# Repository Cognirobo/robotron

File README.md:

# robotron
our first own robot

Welcome to our robotron!!
Here we can handle all documents, scripts and code for our robot
Here is a basic stucture, please feel free to add, edit and extend if it is needed.

**Vision statement:**
We will build a powerful and adaptable Robotplatform 

* Projcect Plan
  * Who is Who and what to do
  * Ideas for the robot and the future
* Mechanical design
  * Calculations and requirements
  * Blueprints for the robot
  * Pictures
* Electrical design
  * Wireing
  * Blueprints of the electrical circuts
  * Pictures
* Code
  * :-) a hell lot of code in c, c++, phyton etc.
* Frond design 
  * drawings how the robot will look
  * Pictures 

**Price**
For all of you who not studied buissnes stuff. The price is important. Make a good robot with cheap stuff then it will be fantastic with expensive components.

**RoboLution:** Here everyone can see what we have after each Hackday, this we call the RoboLution.

* fist Hackday
https://github.com/Cognirobo/robotron/blob/master/projectplan/2016_04_23_Hackday/images/RoboLution_1.avi

* second Hackday
https://github.com/Cognirobo/robotron/blob/master/projectplan/2016_05_16_Hackday/images/RoboLution_2.avi

* third Hackday
https://github.com/Cognirobo/robotron/blob/master/projectplan/2016_05_26_Hackday/images/RoboLution_3.avi

* fourth Hackday
https://github.com/Cognirobo/robotron/blob/master/projectplan/2016_06_19_Hackday/images/RoboLution_4.avi

**Have fun with Markdown to make it look really cool**
  
https://guides.github.com/features/mastering-markdown/

**Nice tool for windows to see the branches and commits**

https://desktop.github.com/

**Nice tool to make UML and other charts**

http://de.plantuml.com/
and the online version:
http://www.planttext.com/planttext

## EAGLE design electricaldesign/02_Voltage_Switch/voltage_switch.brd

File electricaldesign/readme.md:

#Proposal for the Powersupply

In order to work good with the robot,
As a developer I need to connect the robot to a 230V energy supply or a battery.

Side conditions:
* switch from battery to main voltage when the 230V supply is connected
* has until now two different current levels: 
  * approximal 15 V for Arduino and elecrtical drive
  * approximal 5 V for everything with USB PI
* overall energy consumption is not clear and has to be investigated

Plaesa note: The files with the ending .sch can be opend via eagle

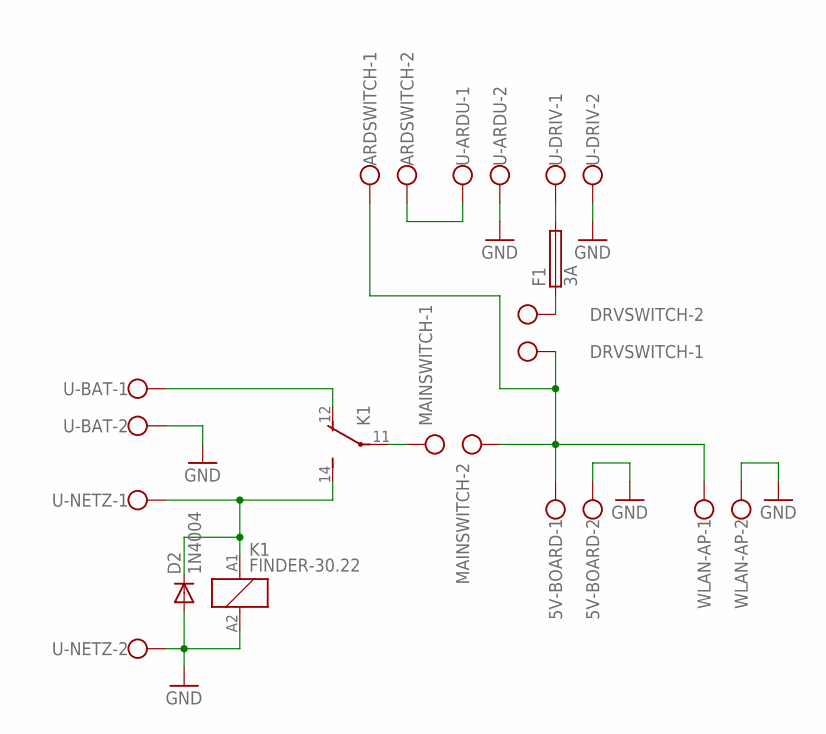
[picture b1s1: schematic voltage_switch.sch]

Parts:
5V-BOARD: W237-102
ARDSWITCH: W237-102
D2: 1N4004; DO41-10
DRVSWITCH: W237-102
F1: 3A; GSH15
K1: FINDER-30.22
MAINSWITCH: W237-102
U-ARDU: W237-102
U-BAT: W237-102
U-DRIV: W237-102
U-NETZ: W237-102
WLAN-AP: W237-102

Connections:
GND: 5V-BOARD.2, D2.A, K1.A2 (2), U-ARDU.2, U-BAT.2, U-DRIV.2, U-NETZ.2, WLAN-AP.2
unnamed: D2.C, K1.14 (S), K1.A1 (1), U-NETZ.1
unnamed: K1.11, MAINSWITCH.1
unnamed: K1.12 (O), U-BAT.1
unnamed: DRVSWITCH.2, F1.1
unnamed: 5V-BOARD.1, ARDSWITCH.1, DRVSWITCH.1, MAINSWITCH.2, WLAN-AP.1
unnamed: F1.2, U-DRIV.1
unnamed: ARDSWITCH.2, U-ARDU.1

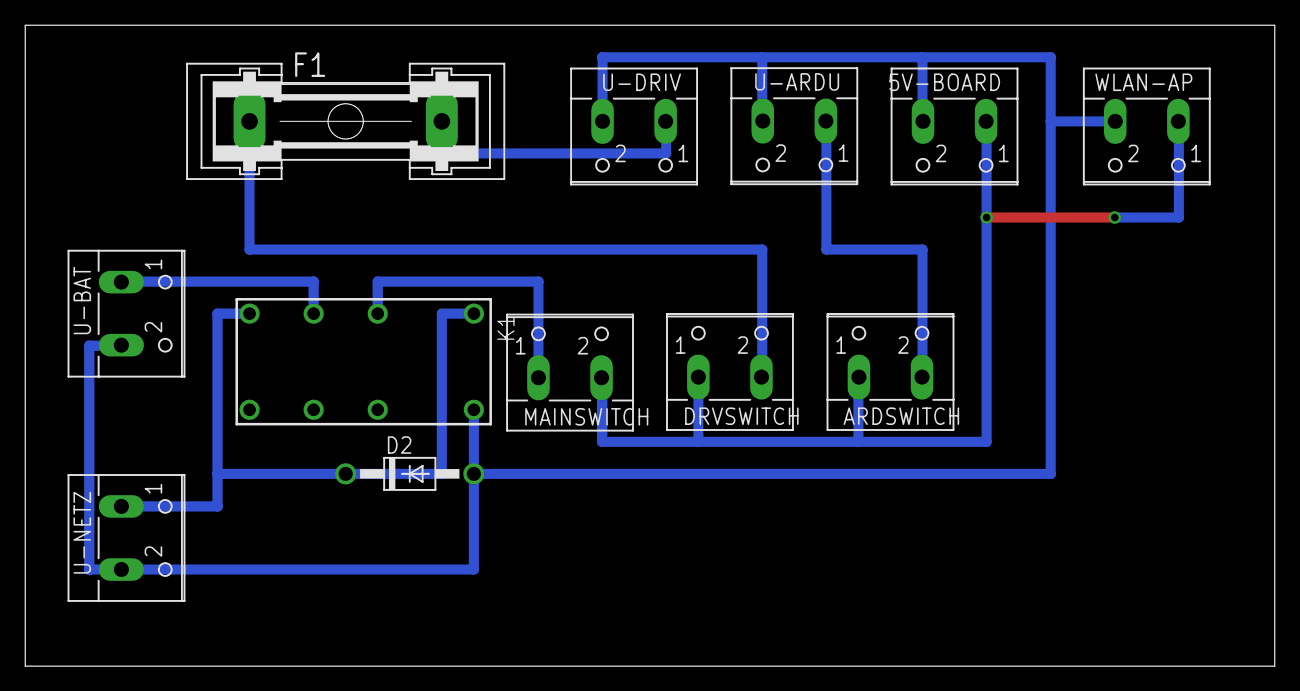
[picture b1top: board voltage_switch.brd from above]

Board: 2 copper layers, 99.0 x 50.8 mm, 12 parts (0 on the bottom side), 8 nets.

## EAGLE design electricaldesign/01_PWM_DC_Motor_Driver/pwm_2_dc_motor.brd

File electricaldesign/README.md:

#Electrical Hardware
There are several boards we need to use our robotron. They are so far:

###PWM DC Motor driver
Uses a PWM signal to drive the two DC motors. Can handle up to 50A and 20V, but needs a cooling device on top.

###Voltage distribution
Gets the voltage to every part of our robotron and is the central board to plugin the batteries or the main supply.

###5V DC
Step-down-regulator to get 5V for the Raspberry Pi.

###Encoder of wheel rpm
Produces a signal with a infrared diode and a infrared transistor so the rpm of ever wheel can be read by the arduino and our robot will drive the way we want it. One board per wheel, but the schematics are the same.

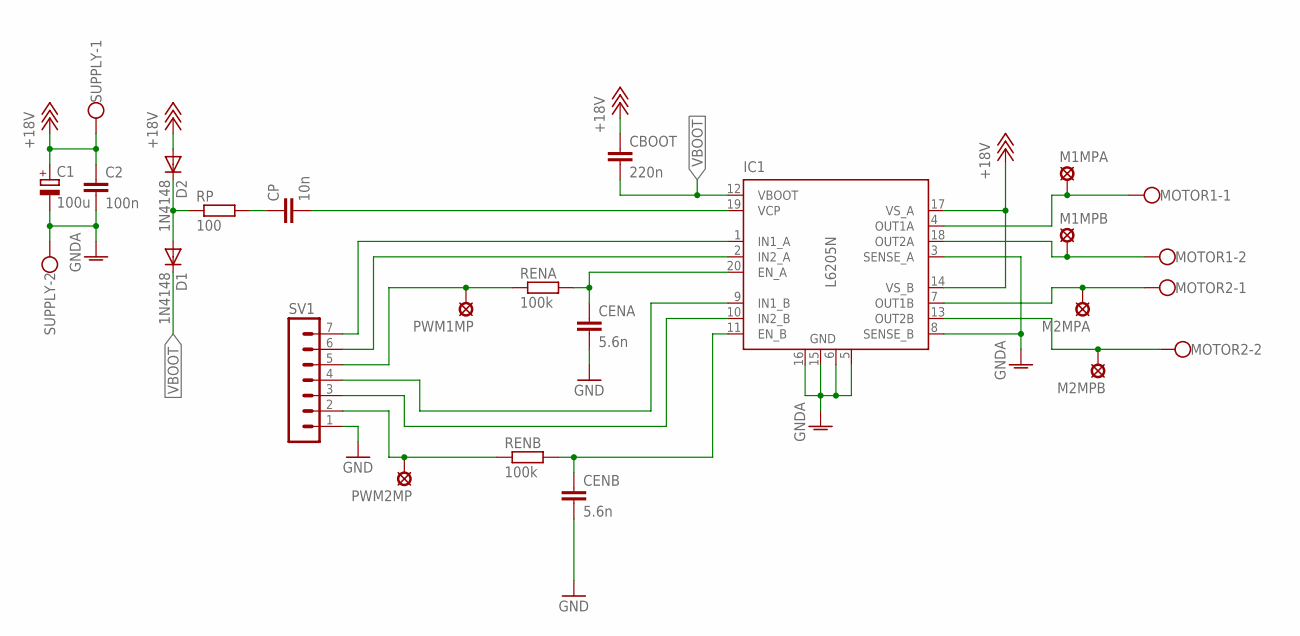
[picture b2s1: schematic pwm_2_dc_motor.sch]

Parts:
C1: 100u; E2,5-6E
C2: 100n; C025-025X050
CBOOT: 220n; C025-025X050
CENA: 5.6n; C025-025X050
CENB: 5.6n; C025-025X050
CP: 10n; C025-025X050
D1, D2: 1N4148; DO35-10
IC1: L6205N; DIL20
M1MPA, M1MPB, M2MPA, M2MPB: LSP10
MOTOR1, MOTOR2: W237-102
PWM1MP, PWM2MP: LSP10
RENA: 100k; 0207/10
RENB: 100k; 0207/10
RP: 100; 0207/12
SUPPLY: W237-102
SV1: MA07-1

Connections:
+18V: C1.+, C2.1, CBOOT.1, D2.A, IC1.14 (VS_B), IC1.17 (VS_A), SUPPLY.1
GND: CENA.2, CENB.2, SV1.1
GNDA: C1.-, C2.2, IC1.3 (SENSE_A), IC1.5 (GND), IC1.6 (GND), IC1.8 (SENSE_B), IC1.15 (GND), IC1.16 (GND), SUPPLY.2
unnamed: IC1.4 (OUT1A), M1MPA.MP, MOTOR1.1
unnamed: IC1.1 (IN1_A), SV1.7
unnamed: IC1.2 (IN2_A), SV1.6
unnamed: PWM1MP.MP, RENA.1, SV1.5
unnamed: IC1.9 (IN1_B), SV1.4
unnamed: IC1.10 (IN2_B), SV1.3
unnamed: CENA.1, IC1.20 (EN_A), RENA.2
unnamed: D1.A, D2.C, RP.1
unnamed: CP.1, RP.2
unnamed: CP.2, IC1.19 (VCP)
unnamed: IC1.18 (OUT2A), M1MPB.MP, MOTOR1.2
unnamed: IC1.7 (OUT1B), M2MPA.MP, MOTOR2.1
unnamed: IC1.13 (OUT2B), M2MPB.MP, MOTOR2.2
unnamed: CENB.1, IC1.11 (EN_B), RENB.2
unnamed: PWM2MP.MP, RENB.1, SV1.2
VBOOT: CBOOT.2, D1.C, IC1.12 (VBOOT)

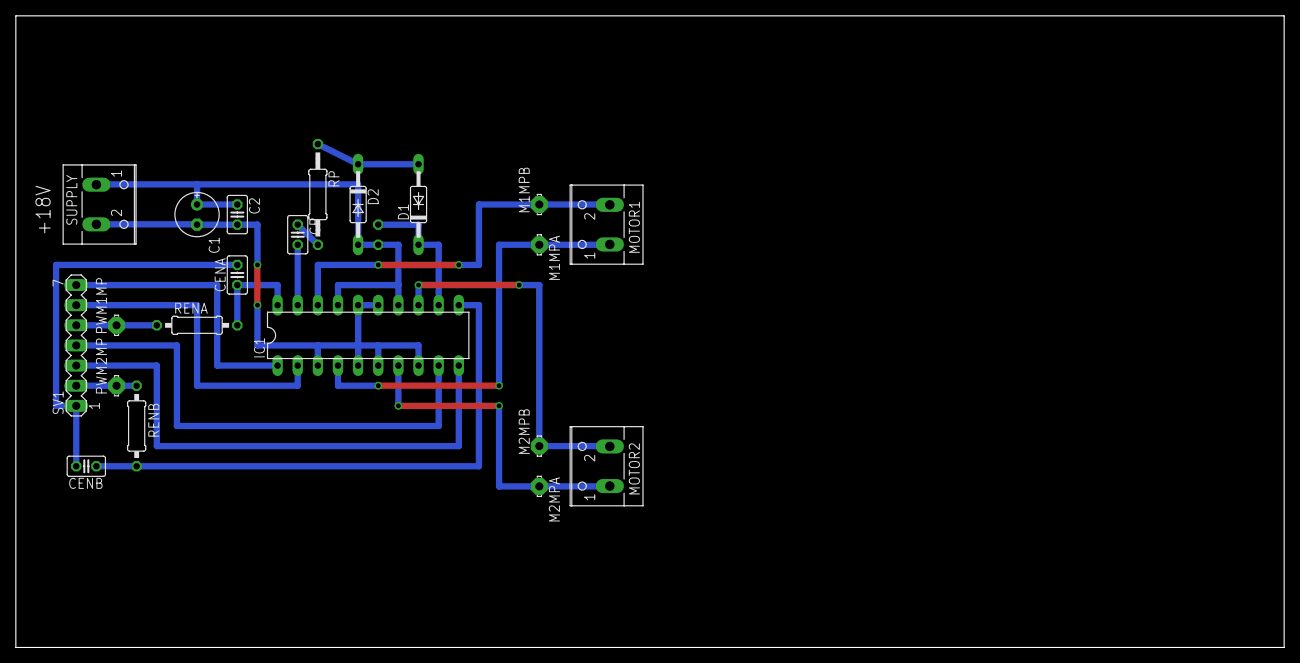
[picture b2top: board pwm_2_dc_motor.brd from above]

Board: 2 copper layers, 160.0 x 79.7 mm, 22 parts (1 on the bottom side), 19 nets.

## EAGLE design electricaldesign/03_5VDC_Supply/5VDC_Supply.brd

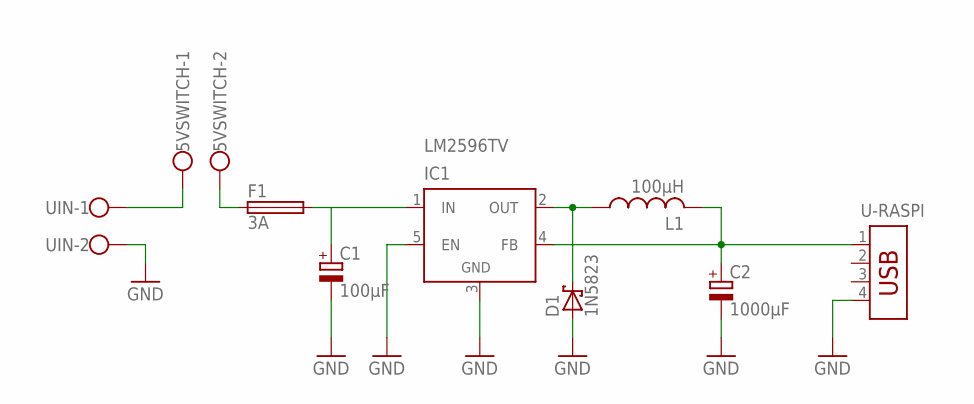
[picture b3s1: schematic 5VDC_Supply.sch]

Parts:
5VSWITCH: W237-102
C1: 100µF; E5-6
C2: 1000µF; E5-10,5
D1: 1N5823; C4111-15
F1: 3A; GSH15
IC1: LM2596TV; TO220-51
L1: 100µH; IRF-3
U-RASPI: USB-787616; USB
UIN: W237-102

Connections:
GND: C1.-, C2.-, D1.A, IC1.3 (GND), IC1.5 (EN), U-RASPI.4, UIN.2
unnamed: 5VSWITCH.1, UIN.1
unnamed: 5VSWITCH.2, F1.1
unnamed: C1.+, F1.2, IC1.1 (IN)
unnamed: D1.C, IC1.2 (OUT), L1.1
unnamed: C2.+, IC1.4 (FB), L1.2, U-RASPI.1

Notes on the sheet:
LM2596TV

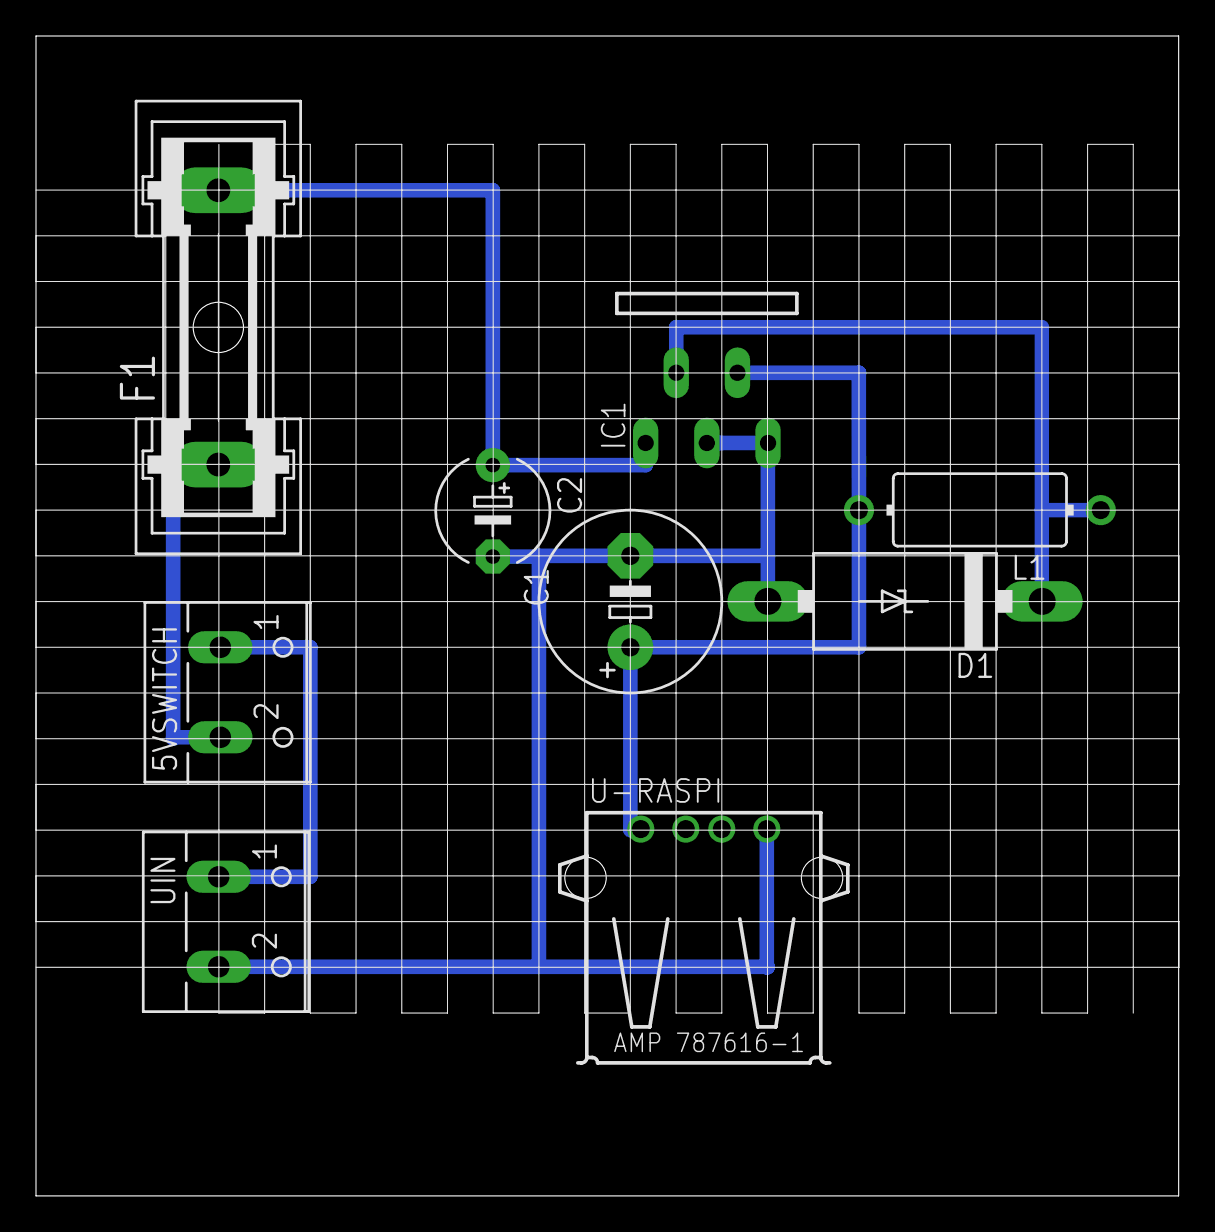
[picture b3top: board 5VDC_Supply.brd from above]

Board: 2 copper layers, 63.5 x 64.4 mm, 9 parts (0 on the bottom side), 6 nets.

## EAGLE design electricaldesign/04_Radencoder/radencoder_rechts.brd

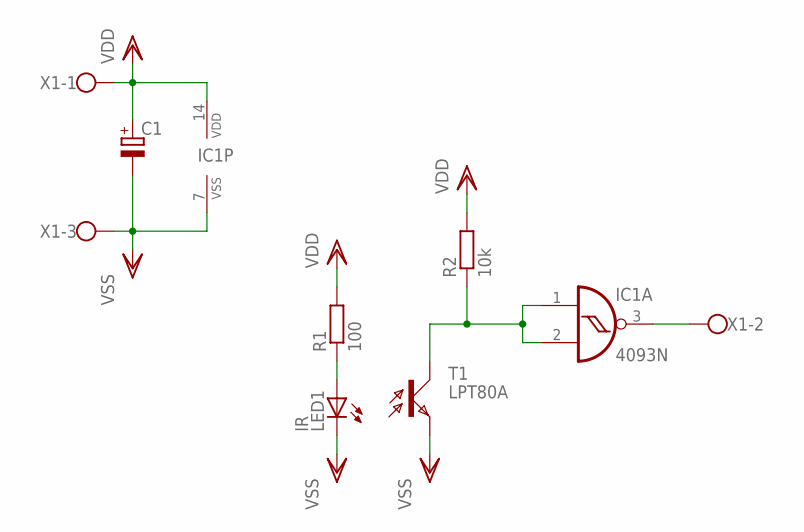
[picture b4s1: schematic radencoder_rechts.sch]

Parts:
C1: CPOL-EUE5-10.5; E5-10,5
IC1: 4093N; DIL14
LED1: IR; LED5MM
R1: 100; 0207/10
R2: 10k; 0207/10
T1: LPT80A
X1: W237-103

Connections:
unnamed: IC1.3 (O), X1.2
unnamed: IC1.1 (I0), IC1.2 (I1), R2.1, T1.C
unnamed: LED1.A, R1.1
VDD: C1.+, IC1.14 (VDD), R1.2, R2.2, X1.1
VSS: C1.-, IC1.7 (VSS), LED1.K (C), T1.E, X1.3

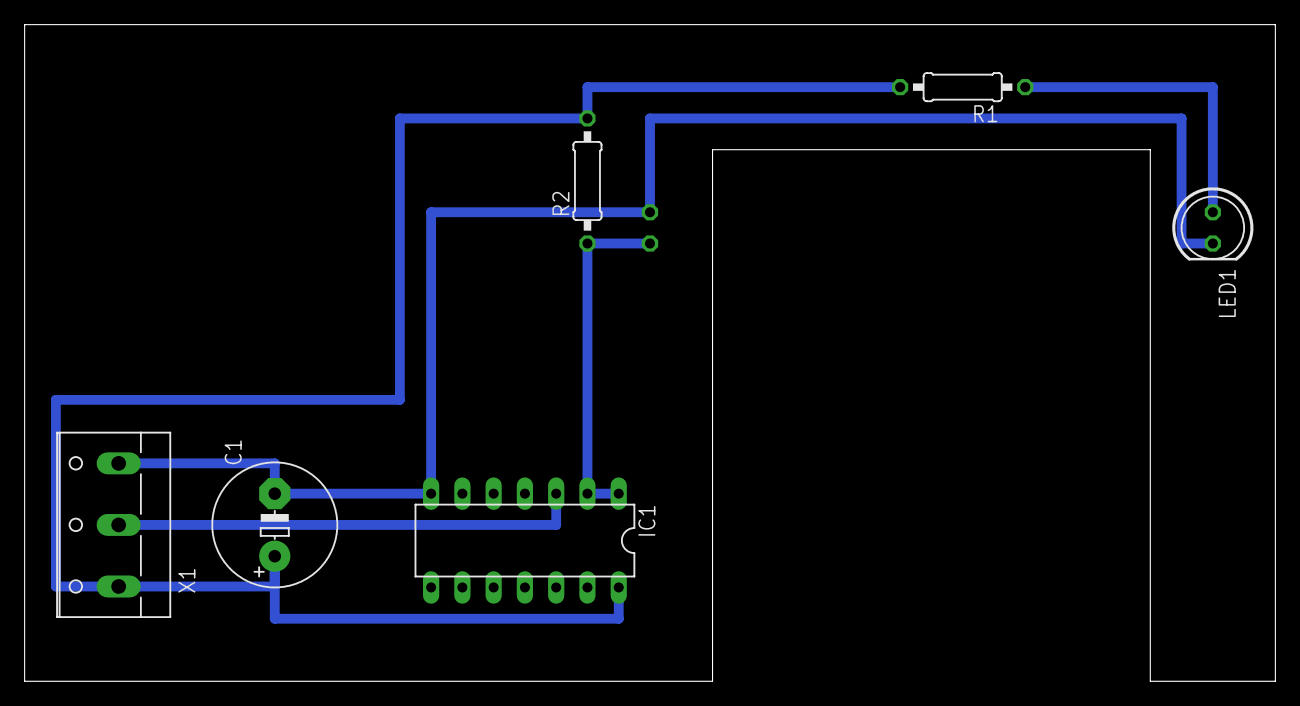
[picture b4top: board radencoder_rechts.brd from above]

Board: 2 copper layers, 101.6 x 53.3 mm, 7 parts (1 on the bottom side), 5 nets.

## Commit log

2016-03-31 Added files via upload
2016-04-04 Create 2016_04_23_Hackday
2016-04-04 Update 2016_04_23_Hackday
2016-04-04 Rename projectplan/readme.md to projectplan/2016_04_23_Hackday/readme.md
2016-04-05 edit it
2016-04-05 changed it back
2016-04-05 add a link
2016-04-23 added src folder
2016-04-23 initial commit for pwm hw test
2016-05-16 altered Project folder
2016-05-16 restiction to markup language fixed
2016-05-16 added Image of chassis
2016-05-16 upload is working
2016-05-16 added movie about our great Wheels
2016-05-16 update clips
2016-05-16 added images and clips from the robot
2016-05-19 added resoures link and serial port script
2016-05-19 added Arduino files for serial and PWM
2016-05-19 clean up
2016-05-19 altered syntax highlighting
2016-05-19 again
2016-05-19 new version full fuctionality of Py controls 1 motor forward/backward
2016-05-21 Version for two motors
2016-05-22 test with motor, teribal emv problems
2016-05-26 updated Hackday Plan for 26.05.2016
2016-05-26 updated again
2016-05-28 App Development How to get the Android Studio Bundle
2016-05-28 some more information
2016-05-28 update what we have done
2016-05-28 serial communication over ssh
2016-05-29 updated README with RoboLution and go.py
2016-05-29 Added Robolution avis
2016-05-29 added pictures from the Hackday
2016-05-29 make README nice again
2016-05-29 update the RoboLution
2016-05-29 Added SSH go.py
2016-05-29 removed old arduino file
2016-05-29 go file
2016-05-29 First App try to share it
2016-05-30 typos fixed
2016-06-02 four buttons to the app
2016-06-02 New App APK with four buttons
2016-06-04 added the ROS things
2016-06-04 hell yeah
2016-06-05 bring up the Arduino via ROS
2016-06-05 update discription for ROS
2016-06-19 the app
2016-06-19 src/app/rosjava_android_template-master/
2016-06-19 App ready for Arduino
2016-06-19 working app and Arduino
2016-06-19 added clip and updated main readme
2016-06-19 updated documentation
2016-06-19 updateed robolution 4
2016-06-19 jaja
2016-06-24 update next hackday
2016-07-02 update for Ideas
2016-08-21 modified: README.md modified: src/arduino/readme.md
2016-08-21 modified: projectplan/next_hack_day/readme.md
2016-08-21 typo
2016-08-21 deleted: .project deleted: projectplan/next_hack_day/readme.md~
2016-08-21 deleted: projectplan/Backlock/readme.md~ deleted: src/app/readme.txt~ deleted: src/raspberry/readme.md~
2016-11-20 removed poti input
2016-11-20 update readme with actuall version von arduino file
2016-11-20 softstarte function
2016-11-22 added circut diagram
2016-12-27 Added blank files to start with and to test the pull request
2016-12-27 wrong filename
2017-01-13 Reorganised the electrical design folder and added all schematics and boards
2017-01-13 Added a new README.md to electrialdesign/
2017-01-13 Typo fixed
